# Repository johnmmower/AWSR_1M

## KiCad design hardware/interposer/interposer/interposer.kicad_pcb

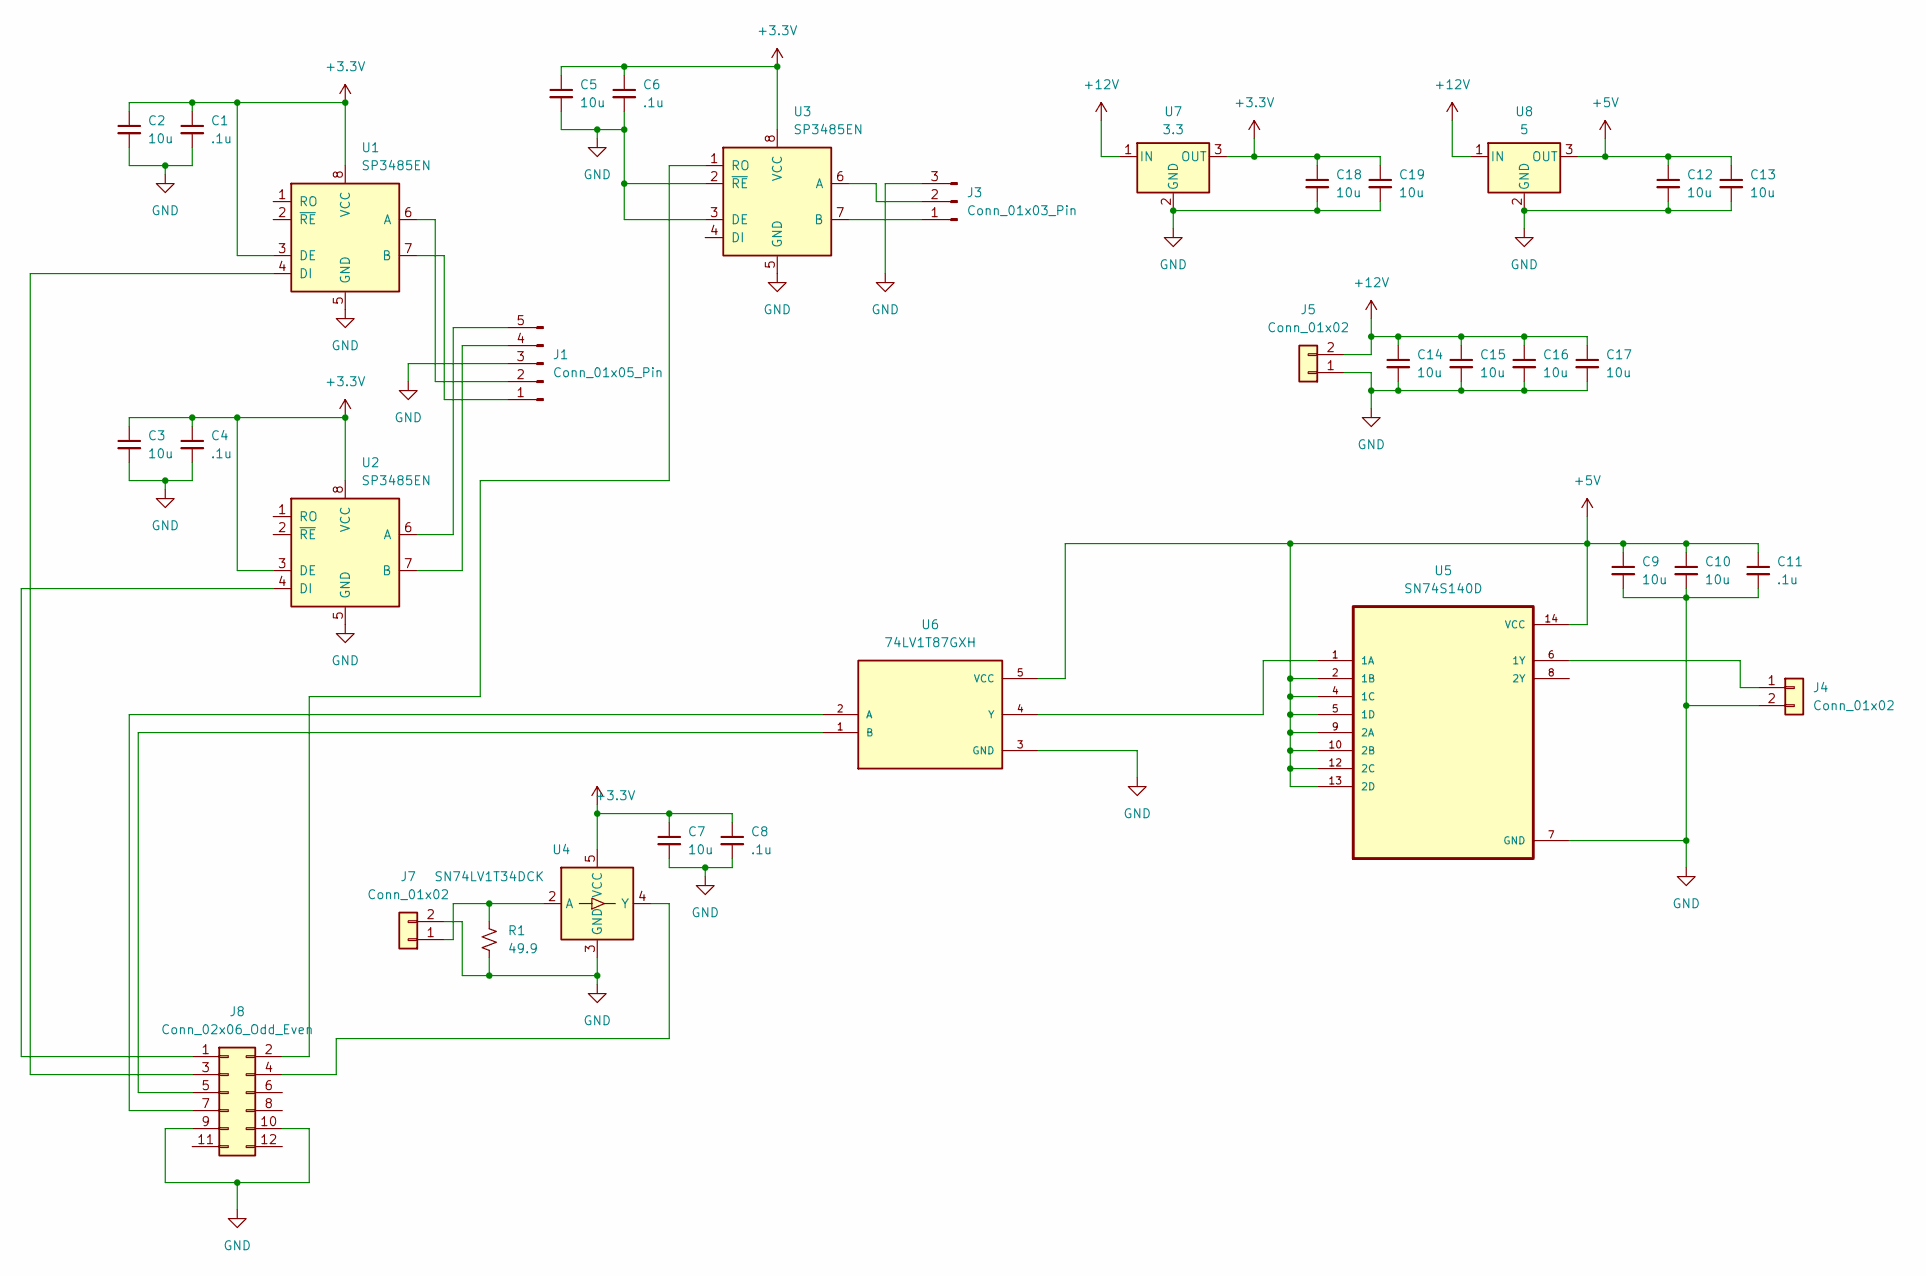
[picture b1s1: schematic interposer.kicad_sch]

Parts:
C1, C4, C6, C8, C11: .1u; C_0805_2012Metric_Pad1.18x1.45mm_HandSolder
C2, C3, C5, C7, C9, C10, C12, C13, C14, C15, C16, C17, C18, C19: 10u; C_0805_2012Metric_Pad1.18x1.45mm_HandSolder
J1: Conn_01x05_Pin; Molex_KK-254_AE-6410-05A_1x05_P2.54mm_Vertical
J3: Conn_01x03_Pin; Molex_KK-254_AE-6410-03A_1x03_P2.54mm_Vertical
J4, J5, J7: Conn_01x02; Molex_KK-254_AE-6410-02A_1x02_P2.54mm_Vertical
J8: Conn_02x06_Odd_Even; PinHeader_2x06_P2.54mm_Vertical
R1: 49.9; R_0805_2012Metric_Pad1.20x1.40mm_HandSolder
U1, U2, U3: SP3485EN; SOIC-8_3.9x4.9mm_P1.27mm
U4: SN74LV1T34DCK; SOT-353_SC-70-5
U5: SN74S140D; SOIC-14_3.9x8.7mm_P1.27mm
U6: 74LV1T87GXH; TSOP-5_1.65x3.05mm_P0.95mm; PARTREV 4
U7: 3.3; TO-220F-3_Vertical
U8: 5; TO-220F-3_Vertical

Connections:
+3.3V: C1.1, C2.1, C3.1, C4.1, C5.1, C6.1, C7.1, C8.1, C18.1, C19.1, U1.3 (DE), U1.8 (VCC), U2.3 (DE), U2.8 (VCC), U3.8 (VCC), U4.5 (VCC), U7.3 (OUT)
+5V: C9.1, C10.1, C11.1, C12.1, C13.1, U5.2 (1B), U5.4 (1C), U5.5 (1D), U5.9 (2A), U5.10 (2B), U5.12 (2C), U5.13 (2D), U5.14 (VCC), U6.5 (VCC), U8.3 (OUT)
+12V: C14.1, C15.1, C16.1, C17.1, J5.2, U7.1 (IN), U8.1 (IN)
GND: C1.2, C2.2, C3.2, C4.2, C5.2, C6.2, C7.2, C8.2, C9.2, C10.2, C11.2, C12.2, C13.2, C14.2, C15.2, C16.2, C17.2, C18.2, C19.2, J1.3, J3.3, J4.2, J5.1, J7.2, J8.9, J8.10, R1.2, U1.5 (GND), U2.5 (GND), U3.2 (~RE), U3.3 (DE), U3.5 (GND), U4.3 (GND), U5.7 (GND), U6.3 (GND), U7.2 (GND), U8.2 (GND)
unnamed: J1.1, U1.7 (B)
unnamed: J1.2, U1.6 (A)
unnamed: J1.4, U2.7 (B)
unnamed: J1.5, U2.6 (A)
unnamed: J3.1, U3.7 (B)
unnamed: J3.2, U3.6 (A)
unnamed: J4.1, U5.6 (1Y)
unnamed: J7.1, R1.1, U4.2 (A)
unnamed: J8.1, U2.4 (DI)
unnamed: J8.2, U3.1 (RO)
unnamed: J8.3, U1.4 (DI)
unnamed: J8.4, U4.4 (Y)
unnamed: J8.5, U6.1 (B)
unnamed: J8.7, U6.2 (A)
unnamed: U5.1 (1A), U6.4 (Y)

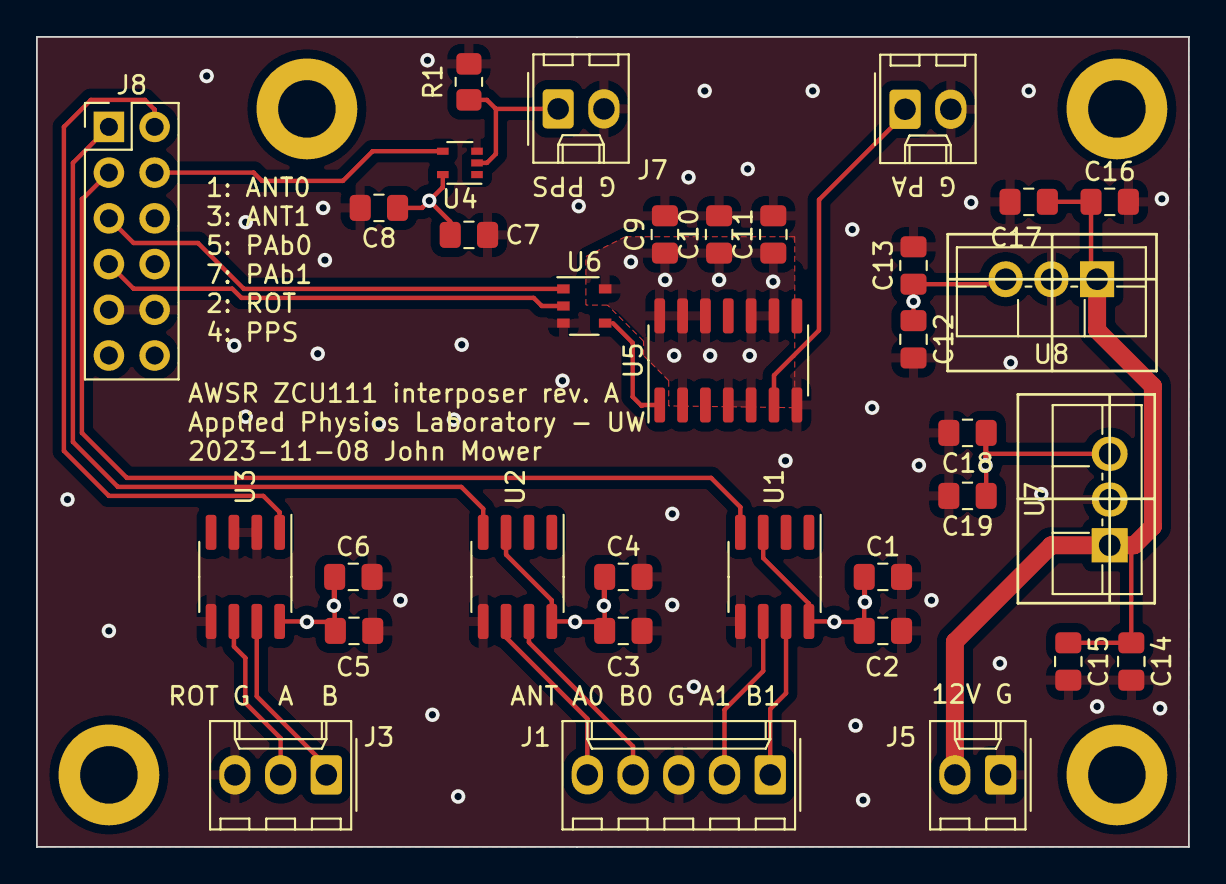
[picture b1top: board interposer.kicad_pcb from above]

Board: 4 copper layers, 64.0 x 45.0 mm, 34 parts (0 on the bottom side), 19 nets.

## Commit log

2023-09-28 clock config blinks 192 src
2023-09-28 added adc0 slow clock, cfg is good at 1536 and 192
2023-09-28 bumped freq to 215.04
2023-09-28 prebuild at 215.04 and sdk src
2023-09-28 updated sma output divider
2023-10-16 working real 10MHz passthrough
2023-10-16 working pulse loopback. shit gain
2023-10-20 working loopback, deterministic!
2023-10-24 working pps from PI and half sec. shift
2023-11-11 added encoder no load
2023-11-12 hold tb
2023-11-15 accumulator testing
2023-11-15 tested accumulator fully
2023-11-15 nice sim check
2023-11-16 added tcl script
2023-11-16 restructure
2023-11-16 more restructure
2023-11-16 more restructure for big project
2023-11-16 fixed up tcl
2023-11-16 added variable accumulator samples
2023-11-16 added no sum path
2023-11-17 rx_packer
2023-11-18 tested rx_packer module
2023-11-18 added smoothing to encoder input
2023-11-18 added (and increased bus, decreased clock) 2nd rx dma path
2023-11-18 added tready and error to rx_packer
2023-11-18 forgot to hook up IPI to new DMA
2023-11-20 hmm. need to refactor accumulator
2023-11-21 better accumulator for single shots
2023-11-21 tweaks to accumulator
2023-11-21 updated rx-packer
2023-11-21 working on trigger, stop
2023-11-28 trigger figured out, blanking good
2023-12-05 removed encoder valid, just steady state
2023-12-05 tx addressing added
2023-12-07 need to update control block
2023-12-08 added full control
2023-12-08 missing .vh to project
2023-12-08 added timestamp, fixed typos control
2023-12-08 typos
2023-12-13 timing and pmod1-3 is now paen monitor port
2023-12-15 time for the refactor
2023-12-15 pre refactor test
2023-12-15 refactor prebuild check
2023-12-19 prebuild imported design with ipi route of ddr4
2023-12-20 trying DDR with common base addr and fixed flipped header
2023-12-20 fixed packer, accumulator has issues
2023-12-23 dma sorted, needed a soft reset
2023-12-23 tx and rx acq.
2023-12-31 moving jumble of python to backburner
2023-12-31 working adaptive plus minus
2024-01-01 prepush of python async test
2024-01-02 adaptive python start
2024-01-02 added in cal freeze logic, prebuild
2024-01-03 typo in control.v
2024-01-03 typo in proc.v
2024-01-03 fixed up adaptive python for test
2024-01-03 fixing cal freeze
2024-01-03 working towards cal and freeze
